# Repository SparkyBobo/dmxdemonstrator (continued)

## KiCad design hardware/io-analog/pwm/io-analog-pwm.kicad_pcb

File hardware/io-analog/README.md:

# DMX Demonstrator Analog IO Modules (DMX-IO2, DMX-IO3, DMX-IO4, DMX-IO5)

## Overview

The Analog IO Modules are a family of modules which generate analog signals. These modules are for use with the Receiver IO Module (DMX-RX2) and other DMX Demonstrator components. The Core module (DMX-IO2) convert the DMX signal into a 0 to +2.5V signal which the other modules then use to generate (more) useful signals. The other modules stack on top of the Core module and are designed to by used at the same time, so you can create a stack of any number of modules with DMX-IO2 on the bottom to generate a variety of signals. Each module will produce its signal in response to channels 1-4 and you can any of the signals, just pick off the signal you want from the appropriate module to control a device. You might use a stack of multiple modules if you wanted to coordinate channels 1-4 to control a variety of devices working in unison, such as a DIY moving head fixture.

## Signal options

### Core Module (DMX-IO2)

The Core module (DMX-IO2) convert the DMX signal into a 0 to +2.5V signal which the other modules then use to generate (more) useful signals. You can use the signal directly via the IO extension header.

### Voltage Module (DMX-IO3)

The Voltage IO module can generate a 0 to adjustable positive voltage which tracks the level of a channel. It is configurable to generate multiple output voltages to adapt it to any voltage range required. The default values
listed in the schematic generate 0 to +10V since this is a common lighting control signal.

### PWM Module (DMX-IO4)

The PWM IO module can generate a 0 to adjustable positive voltage PWM signal where the duty cycle tracks the level of a channel. It is configurable to generate multiple output voltages to adapt it to any voltage range required. The default values
listed in the schematic generate 0 to +10V since this is a common lighting control signal. The PWM IO module can also generate a 0 to +5V PWM signal where the duty cycle tracks the level of a channel. Both outputs can be used at the same time.

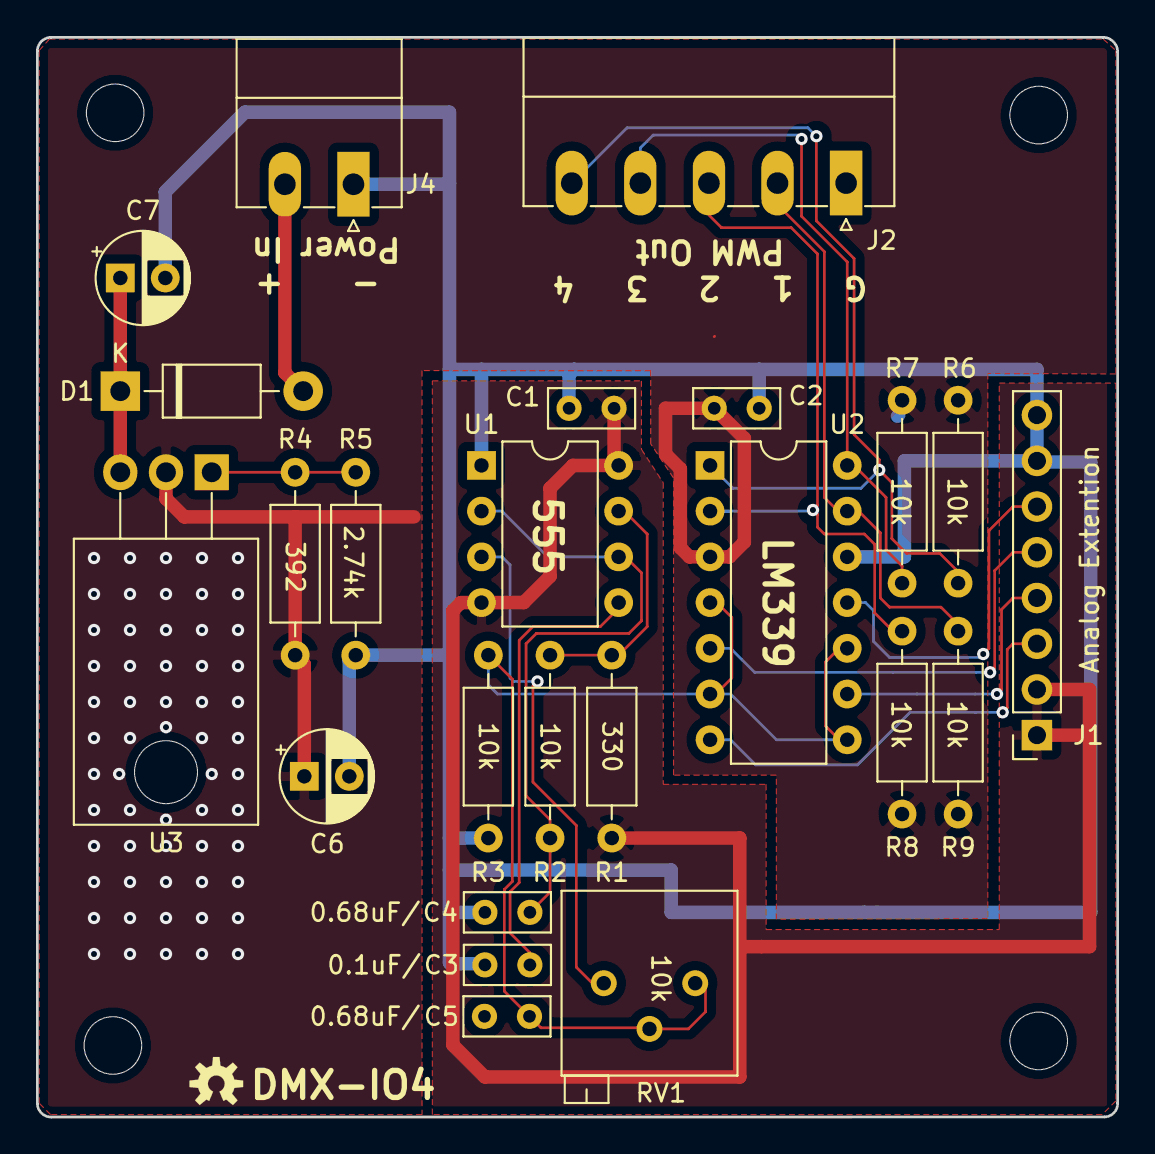
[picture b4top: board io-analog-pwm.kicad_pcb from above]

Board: 2 copper layers, 60.0 x 60.0 mm, 28 parts (0 on the bottom side), 19 nets.

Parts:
C1, C2, C3: 0.1uF; C_Rect_L4.6mm_W2.0mm_P2.50mm_MKS02_FKP02
C4, C5: 0.68uF; C_Rect_L4.6mm_W2.0mm_P2.50mm_MKS02_FKP02
C6, C7: 10uF; CP_Radial_D5.0mm_P2.50mm
D1: 1N5819; D_DO-41_SOD81_P10.16mm_Horizontal
J1: Analog Extension; PinSocket_1x08_P2.54mm_Vertical
J2: Output; PhoenixContact_MC_1,5_5-G-3.81_1x05_P3.81mm_Horizontal
J4: Power; PhoenixContact_MC_1,5_2-G-3.81_1x02_P3.81mm_Horizontal
MH1, MH2, MH3, MH4: MountingHole; MountingHole_3.2mm_M3
R1: 330; R_Axial_DIN0207_L6.3mm_D2.5mm_P10.16mm_Horizontal
R2, R3, R6, R7, R8, R9: 10k; R_Axial_DIN0207_L6.3mm_D2.5mm_P10.16mm_Horizontal
R4: 392 1%; R_Axial_DIN0207_L6.3mm_D2.5mm_P10.16mm_Horizontal
R5: 2.74k 1%; R_Axial_DIN0207_L6.3mm_D2.5mm_P10.16mm_Horizontal
RV1: 10k; Potentiometer_Bourns_3299P_Horizontal
U1: NE555; DIP-8_W7.62mm
U2: LM339; DIP-14_W7.62mm
U3: LM317T; TO-220-3_Horizontal_TabDown

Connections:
+5V: C1.1, J1.1, J1.2, R1.1, U1.4, U1.8
/AO0: J1.6, U2.11
/AO1: J1.5, U2.5
/AO2: J1.4, U2.9
/AO3: J1.3, U2.7
GND: C1.2, C2.2, C3.1, C4.1, C5.2, C6.2, C7.2, J1.7, J1.8, J2.1, J4.1, R3.1, R5.1, U1.1, U2.12
unnamed: C3.2, U1.5
unnamed: C4.2, R2.2, U1.2, U1.6
unnamed: C5.1, R3.2, RV1.2, RV1.3, U2.4, U2.6, U2.8, U2.10
unnamed: C7.1, D1.1, U3.3
unnamed: D1.2, J4.2
unnamed: J2.2, R9.2, U2.13
unnamed: J2.3, R8.2, U2.2
unnamed: J2.4, R7.2, U2.14
unnamed: J2.5, R6.2, U2.1
unnamed: R1.2, R2.1, U1.7
unnamed: R4.1, R5.2, U3.1
unnamed: RV1.1, U1.3
VDC: C2.1, C6.1, R4.2, R6.1, R7.1, R8.1, R9.1, U2.3, U3.2

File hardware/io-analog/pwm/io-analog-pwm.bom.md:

# Bill Of Materials (BOM)

## Schematic

**Filename:** E:\OpenSource\dmxdemonstrator\hardware\io-analog\pwm\io-analog-pwm.sch

**Date Modified:** 4/11/2024 8:56:17 PM

**Kicad Version:** Eeschema (5.1.12)-1

**Component Count:** 25

## Components

Item#|Quantity|Reference|Description|Manufacturer|Part Number|Datasheet|Notes
-----|--------|---------|-----------|------------|-----------|---------|-----
1|1|PCB|Analog IO PWM PCB|OHSPark|DMX-IO4, Rev 1.4||[Order](https://oshpark.com/shared_projects/xqcuVAnE)|
2|3|C1, C2, C3|0.1uF||||
3|2|C4, C5|0.68uF||||
4|2|C6, C7|10uF||||
5|1|D1|Schottky Diode, 40V 1A|Vishay General Semiconductor|1N5819|[Data Sheet](http://www.vishay.com/docs/88525/1n5817.pdf)|
6|1|J1|0.1 Female header, stacking||||
7|1|J2|Screw Terminal, 5 pin, 3.81 pitch|Phoenix Contact|1803303||
8|1|J2|Screw Terminal Plug, 5 pin, 3.81 pitch|Phoenix Contact|1840395||
9|1|J4|Screw Terminal, 2 pin, 3.81 pitch|Phoenix Contact|1803277||
10|1|J4|Screw Terminal Plug, 2 pin, 3.81 pitch|Phoenix Contact|1803578||
11|1|R1|330 ohm||||
12|2|R2, R3|10k ohm||||
13|1|R4|392 ohm 1% resistor||||
14|1|R5|2.74k 1% resistor||||
15|1|RV1|10k trimmer pot|Bourns|3299P-1-103LF|[Data Sheet](https://www.bourns.com/docs/Product-Datasheets/3299.pdf)|
16|1|U1|555 Precision Timer|Texas Instruments|NE555|[Data Sheet](https://www.ti.com/lit/ds/symlink/ne555.pdf)|
17|1|U2|Quad Differential Comparator|Texas Instruments|LM339|[Data Sheet](http://www.ti.com/lit/ds/symlink/lm339.pdf)|
18|1|U3|Linear Regulator, Adjustable, 1.5A TO220AB|STMicroelectronics|LM317T|[Data Sheet](http://www.st.com/content/ccc/resource/technical/document/da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|
<!--BOMROW-->

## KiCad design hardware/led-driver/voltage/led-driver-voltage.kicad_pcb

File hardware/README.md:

# DMX Demonstrator Hardware

## Overview

The DMX Demonstrator hardware folder contains various transmitters, receivers, and modules which all for the control of brightness of 4 channels of dimming.

## Status

Each hardware folder will contain a readme explaining the details of the component and it's status. The following is a definition of some common status:

- 

The _verified_ badge indicates that the component has been built and tested for use with the DMX Demonstrator family and is safe to build.

- 

The _testing_ badge indicates that the component has completed the design and prototype phase and being verified for use with the DMX Demonstrator family. It usually is assigned to a component revision for which the previous version is _verified_.

- 

The _prototype_ badge indicates that the component has completed the design phase and is being built and tested for use with the DMX Demonstrator family.

- 

The _design_ badge indicates that the component is still being design. has completed the design phase.

## Compatibility

For the components which connect to an Arduino, the readme provides a list of known compatible Arduino platforms. The DMX Demonstrator family will likely work with most Arduino boards, real or clones, but if you are having an
[issue](https://github.com/SparkyBobo/dmxdemonstrator/issues) with a particular board, open an issue to ask for verification. Please provide as much detail on the board and where is was obtained as possible.
Most compatibility issues are resolved by updating the software and do not require hardware revisions.

The following is a definition of some compatibilities:

- 

The _verified_ badge indicates that the component has been built and tested for the specific Arduino board.

- 

The _testing_ badge indicates that the component is being tested to determine if it is compatible with the specific Arduino board.

- 

The _research_ badge indicates that the component is being researched to determine if it is compatible with the specific Arduino board.

- 

The _incompatible_ badge indicates that the component is not compatible for the specific Arduino board.

## PCBs and Parts

I specify specific parts and pcbs in many places where other options will work just fine. You can find some notes as to why in [pcb.md](pcb.md) and [parts.md](parts.md).

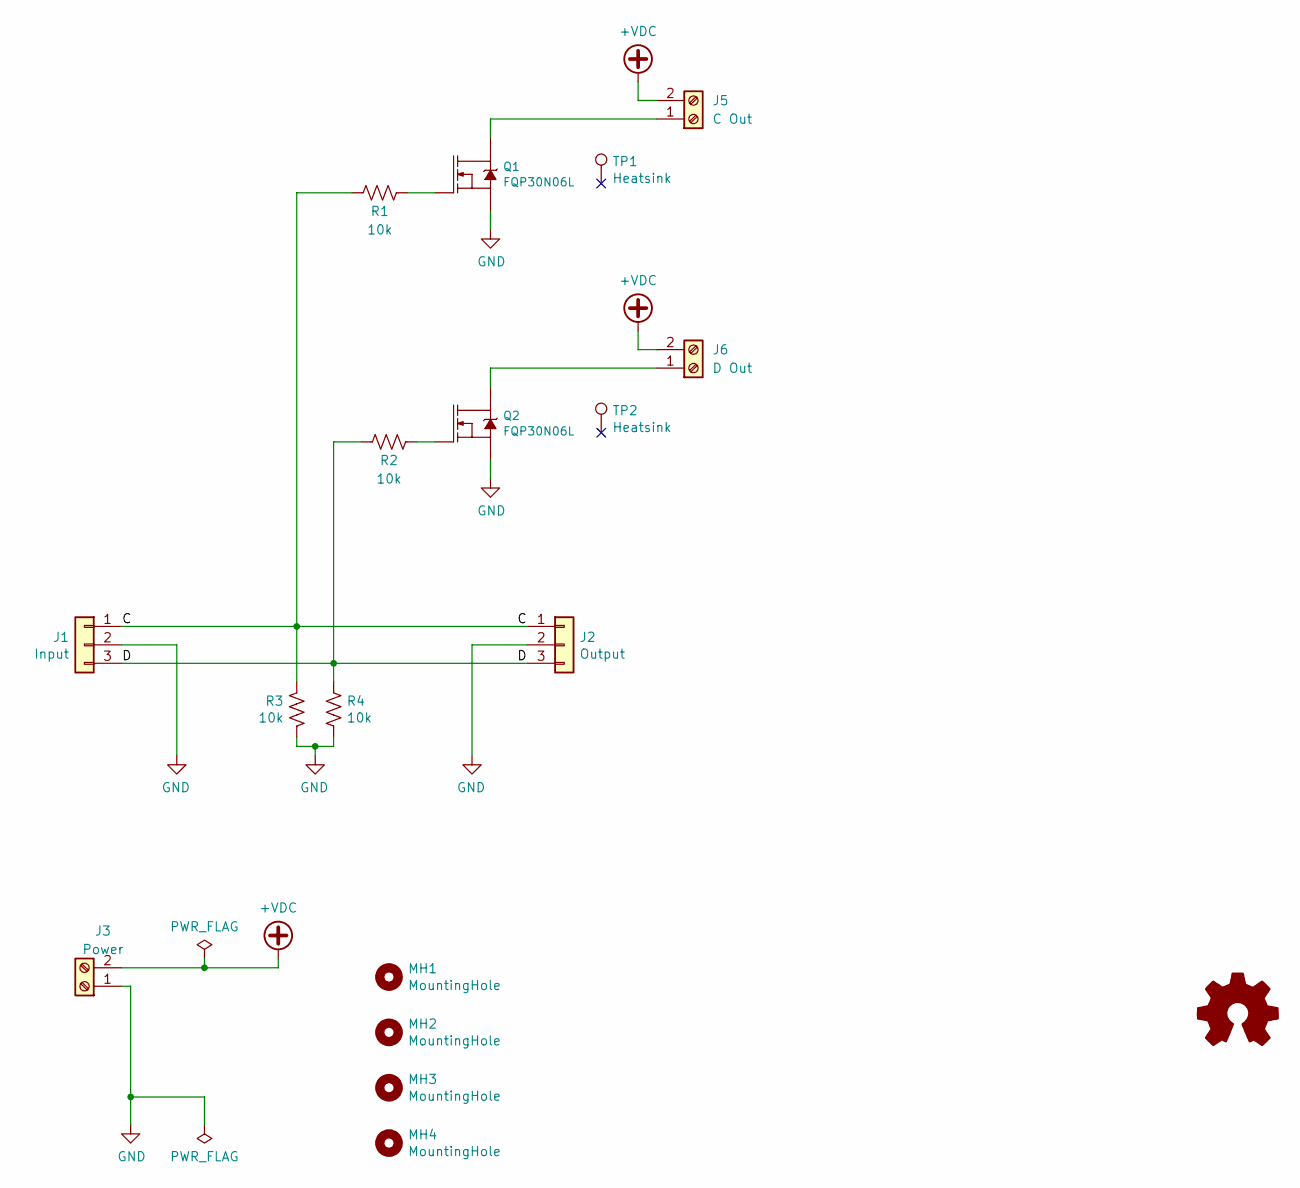
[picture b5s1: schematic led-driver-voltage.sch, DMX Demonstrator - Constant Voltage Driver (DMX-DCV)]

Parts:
J1: Input; PinHeader_1x03_P2.54mm_Horizontal
J2: Output; PinHeader_1x03_P2.54mm_Horizontal
J3: Power; PhoenixContact_MC_1,5_2-G-3.81_1x02_P3.81mm_Horizontal
J5: C Out; PhoenixContact_MC_1,5_2-G-3.81_1x02_P3.81mm_Horizontal
J6: D Out; PhoenixContact_MC_1,5_2-G-3.81_1x02_P3.81mm_Horizontal
MH1, MH2, MH3, MH4: MountingHole; MountingHole_3.2mm_M3
Q1, Q2: FQP30N06L; TO-220-3_Horizontal_TabDown
R1, R2, R3, R4: 10k; R_Axial_DIN0207_L6.3mm_D2.5mm_P10.16mm_Horizontal
TP1, TP2: Heatsink; TestPoint_Pad_D1.0mm

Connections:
+VDC: J3.2, J5.2, J6.2
/C: J1.1, J2.1, R1.2, R3.2
/D: J1.3, J2.3, R2.2, R4.1
GND: J1.2, J2.2, J3.1, Q1.3 (S), Q2.3 (S), R3.1, R4.2
unnamed: J5.1, Q1.2 (D)
unnamed: J6.1, Q2.2 (D)
unnamed: Q1.1 (G), R1.1
unnamed: Q2.1 (G), R2.1

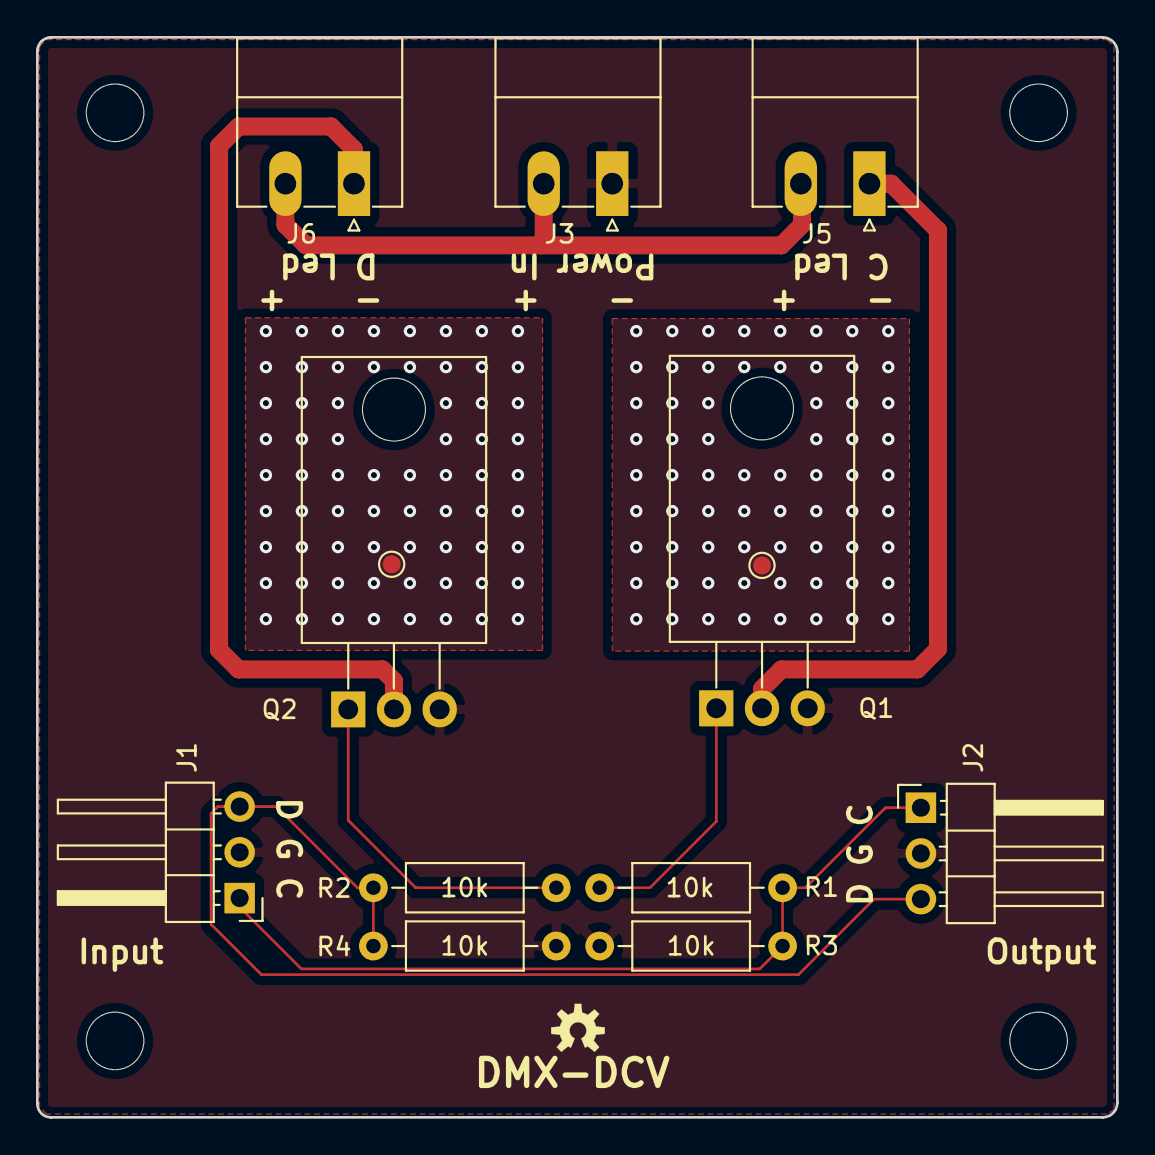
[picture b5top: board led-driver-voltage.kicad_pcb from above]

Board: 2 copper layers, 60.0 x 60.0 mm, 17 parts (0 on the bottom side), 8 nets.

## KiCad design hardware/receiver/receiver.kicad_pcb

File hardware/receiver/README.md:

# DMX Demonstrator Receiver (DMX-RX1)

## Status : Testing

## Overview

The Receiver is an [Arduino](https://www.arduino.cc/) Shield which accepts the 3-wire data/clock signal from the Transmitter (DMX-TX1) and decodes the data stream to control the brightness of 4 LEDs.

## Online parts list

For a complete list of parts, see:

- [Bill of materials](receiver.bom.md)
- [Part lists](receiver.parts.md)

You can also buy the parts for the Receiver online from a Wishlist:

- Sparkfun: [Common](https://www.sparkfun.com/wish_lists/160406), [DMX-RX1](https://www.sparkfun.com/wish_lists/160542)
- Adafruit: [Common](http://www.adafruit.com/wishlists/589832), [DMX-RX1](https://www.adafruit.com/wishlists/589834)

The Receiver needs parts from the common parts list but there are enough parts left over to build a Transmitter (DMX-TX1), Transmitter IO (DMX-TX2), and Frame Scrambler (DMX-FS1).

## PCB

You can order the PCB from [OHS Park](https://oshpark.com/):

- [DMX-RX1, Rev 1.4](https://oshpark.com/shared_projects/KHwUs20e).

You can read more about ordering pcbs [here](../pcb.md).

- ## Compatibility

 The DMX-RX1 is compatible with the following Arduino platforms:

- Arduino Uno R3: Hardware Revision 1.1+, Software Version 1.1+
- Arduino Leonardo: Hardware Revision 1.1+, Software Version  1.1+
- Arduino Mega or Mega 2560: Hardware Revision 1.1+, Software Version 1.2+

## Version History

### Rev 1.4

- Add PWM headers for use with led drivers

### Rev 1.3

- Remove PWM connector

### Rev 1.2

- Moved clock LED to avoid Arduino ICSP connector.
- Add RXCLK to D9 connection for Leonardo PCINT5.

### Rev 1.1

- Fixed shield footprint
- Added error and start code LEDs.
- Added Fcu power plane
- Redid Fcu layout
- Added rounded corners

### Rev 1.0

- Initial draft

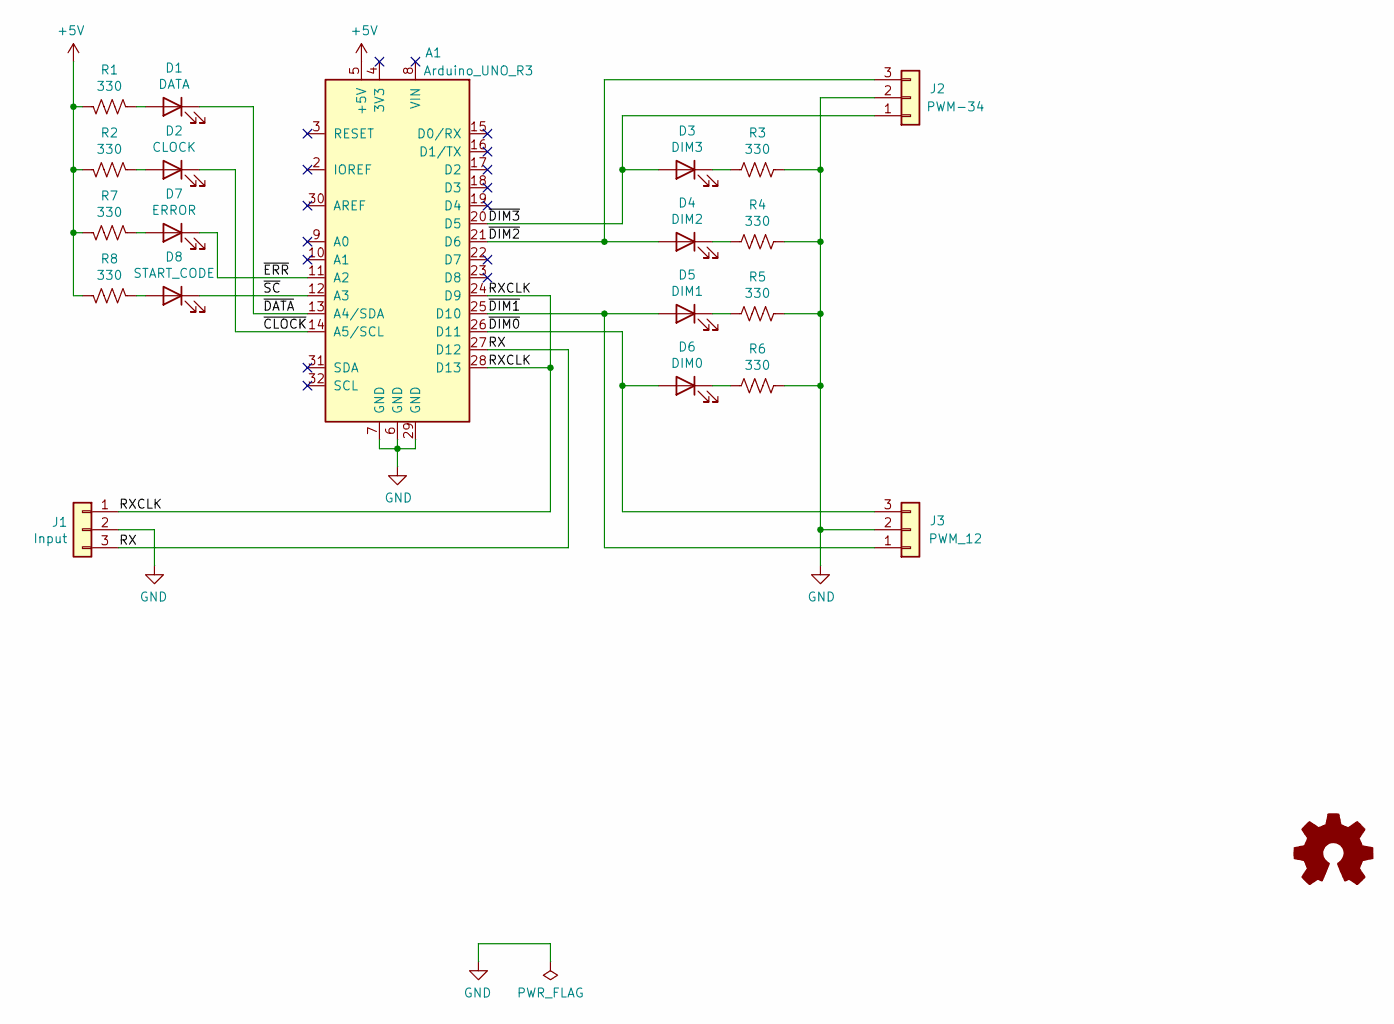
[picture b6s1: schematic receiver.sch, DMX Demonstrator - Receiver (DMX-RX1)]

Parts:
A1: Arduino_UNO_R3; ARDUINO_R3_NO_HOLES
D1: DATA; LED_D5.0mm
D2: CLOCK; LED_D5.0mm
D3: DIM3; LED_D5.0mm
D4: DIM2; LED_D5.0mm
D5: DIM1; LED_D5.0mm
D6: DIM0; LED_D5.0mm
D7: ERROR; LED_D5.0mm
D8: START_CODE; LED_D5.0mm
J1: Input; PinHeader_1x03_P2.54mm_Horizontal
J2: PWM-34; PinHeader_1x03_P2.54mm_Horizontal
J3: PWM_12; PinHeader_1x03_P2.54mm_Horizontal
R1, R2, R3, R4, R5, R6, R7, R8: 330; R_Axial_DIN0207_L6.3mm_D2.5mm_P10.16mm_Horizontal

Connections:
+5V: A1.5 (+5V), R1.1, R2.1, R7.1, R8.1
/RX: A1.27 (D12), J1.3
/RXCLK: A1.24 (D9), A1.28 (D13), J1.1
/~CLOCK: A1.14 (A5/SCL), D2.1 (K)
/~DATA: A1.13 (A4/SDA), D1.1 (K)
/~DIM0: A1.26 (D11), D6.2 (A), J3.3
/~DIM1: A1.25 (D10), D5.2 (A), J3.1
/~DIM2: A1.21 (D6), D4.2 (A), J2.3
/~DIM3: A1.20 (D5), D3.2 (A), J2.1
/~ERR: A1.11 (A2), D7.1 (K)
/~SC: A1.12 (A3), D8.1 (K)
GND: A1.6 (GND), A1.7 (GND), A1.29 (GND), J1.2, J2.2, J3.2, R3.1, R4.1, R5.1, R6.1
unnamed: D1.2 (A), R1.2
unnamed: D2.2 (A), R2.2
unnamed: D3.1 (K), R3.2
unnamed: D4.1 (K), R4.2
unnamed: D5.1 (K), R5.2
unnamed: D6.1 (K), R6.2
unnamed: D7.2 (A), R7.2
unnamed: D8.2 (A), R8.2

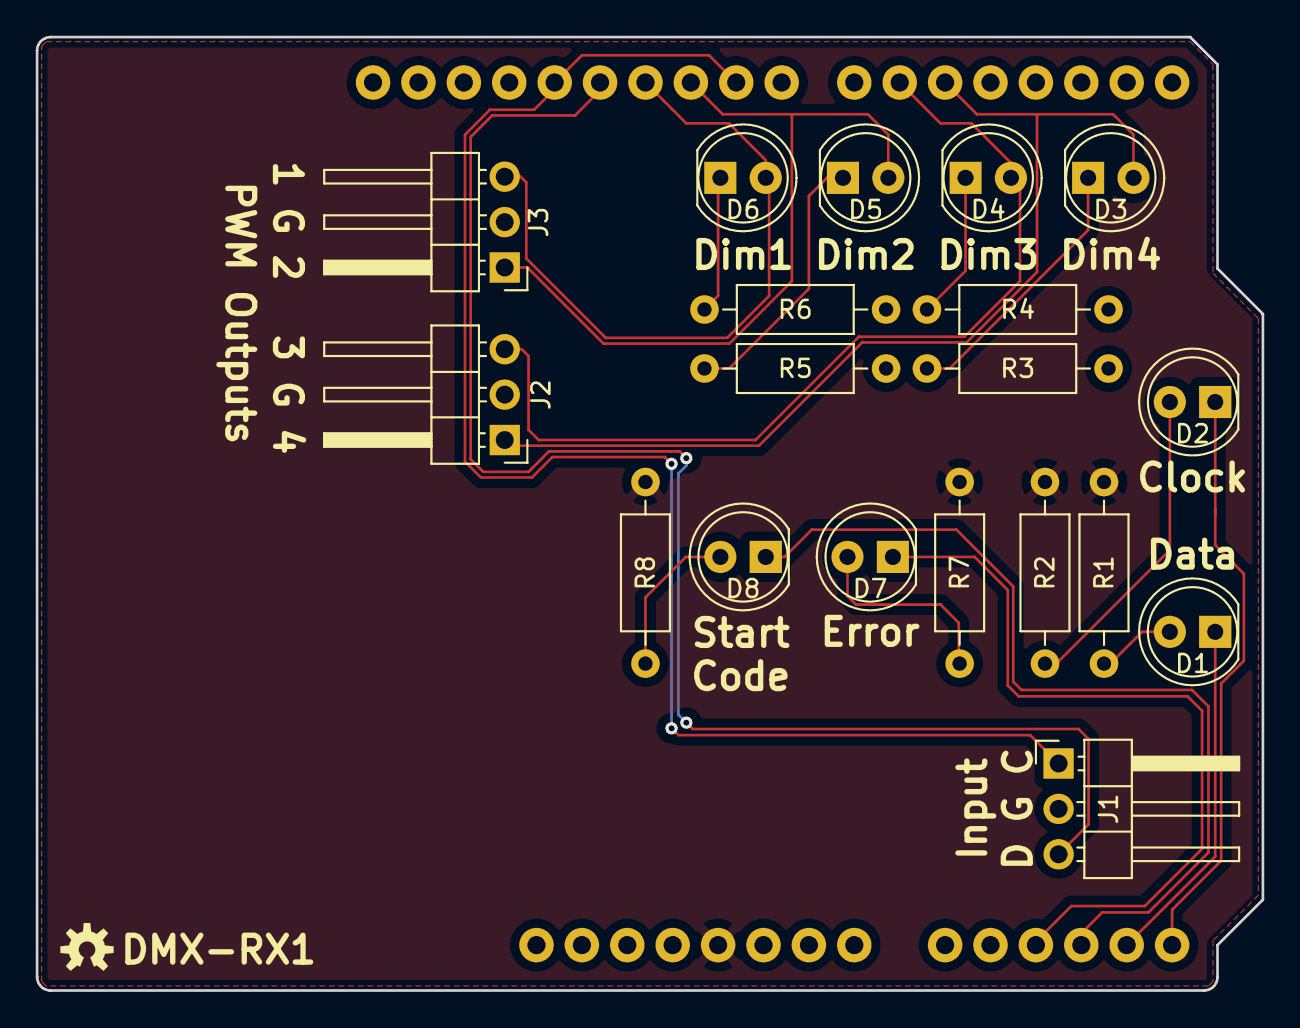
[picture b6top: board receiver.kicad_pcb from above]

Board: 2 copper layers, 68.6 x 53.3 mm, 20 parts (0 on the bottom side), 20 nets.

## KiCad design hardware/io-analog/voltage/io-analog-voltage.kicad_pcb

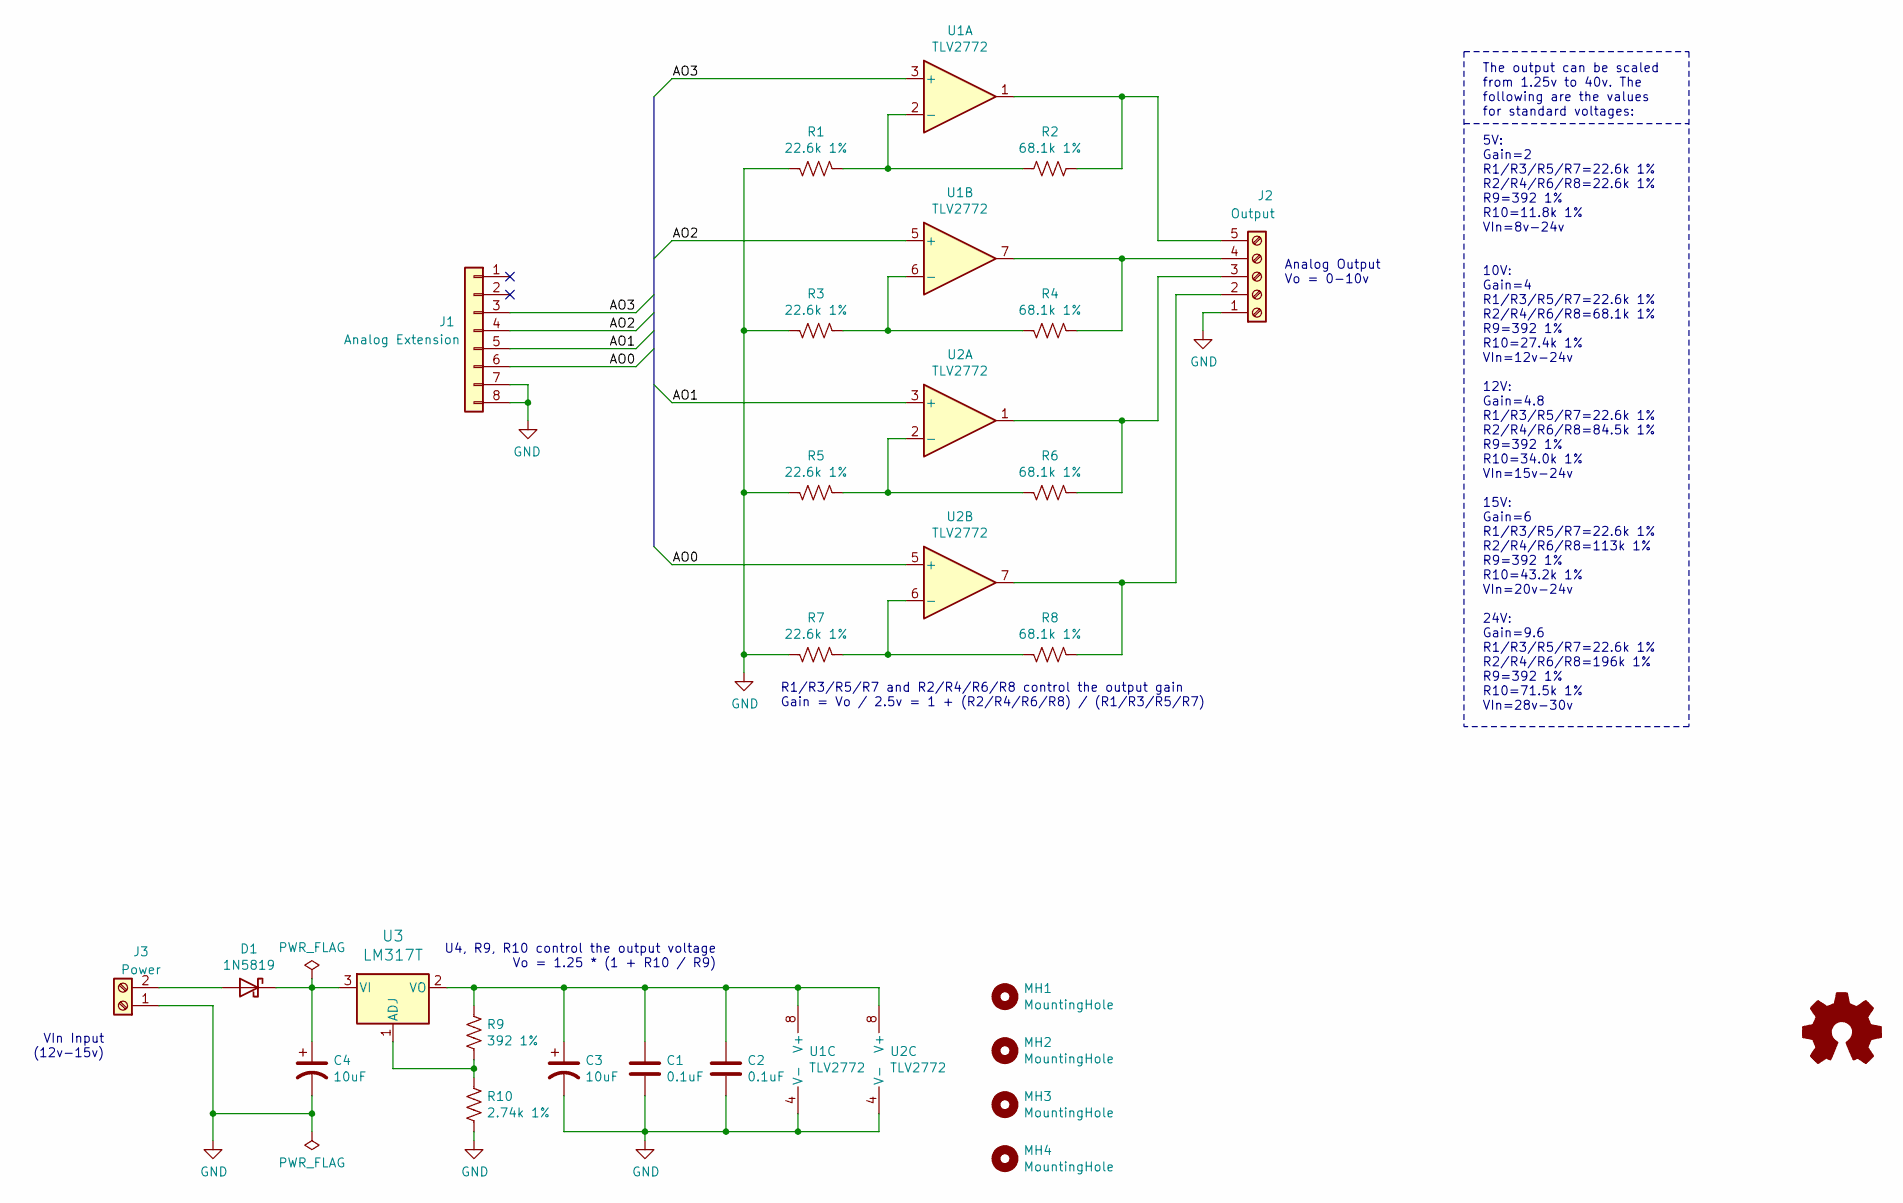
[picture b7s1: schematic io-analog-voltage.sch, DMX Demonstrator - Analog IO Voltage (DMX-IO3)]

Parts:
C1, C2: 0.1uF; C_Rect_L4.6mm_W2.0mm_P2.50mm_MKS02_FKP02
C3, C4: 10uF; CP_Radial_D5.0mm_P2.50mm; Digi-Key_PN P10425CT-ND
D1: 1N5819; D_DO-41_SOD81_P10.16mm_Horizontal; Digi-Key_PN 1N5819-E3/54GITR-ND
J1: Analog Extension; PinSocket_1x08_P2.54mm_Vertical
J2: Output; PhoenixContact_MC_1,5_5-G-3.81_1x05_P3.81mm_Horizontal; Digi-Key_PN 277-1109-ND
J3: Power; PhoenixContact_MC_1,5_2-G-3.81_1x02_P3.81mm_Horizontal; Digi-Key_PN 277-1106-ND
MH1, MH2, MH3, MH4: MountingHole; MountingHole_3.2mm_M3
R1, R3, R5, R7: 22.6k 1%; R_Axial_DIN0207_L6.3mm_D2.5mm_P10.16mm_Horizontal; Digi-Key_PN 22.6KXBK-ND
R2, R4, R6, R8: 68.1k 1%; R_Axial_DIN0207_L6.3mm_D2.5mm_P10.16mm_Horizontal; Digi-Key_PN 68.1KXBK-ND
R9: 392 1%; R_Axial_DIN0207_L6.3mm_D2.5mm_P10.16mm_Horizontal; Digi-Key_PN 392XBK-ND
R10: 2.74k 1%; R_Axial_DIN0207_L6.3mm_D2.5mm_P10.16mm_Horizontal; Digi-Key_PN 13-MFR-25FRF52-2K74TR-ND
U1, U2: TLV2772; DIP-8_W7.62mm; Digi-Key_PN 296-7592-5-ND
U3: LM317T; TO-220-3_Horizontal_TabDown; MPN LM317T; Digi-Key_PN 497-1575-5-ND

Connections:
/AO0: J1.6, U2.5 (+)
/AO1: J1.5, U2.3 (+)
/AO2: J1.4, U1.5 (+)
/AO3: J1.3, U1.3 (+)
GND: C1.2, C2.2, C3.2, C4.2, J1.7, J1.8, J2.1, J3.1, R1.1, R3.1, R5.1, R7.1, R10.1, U1.4 (V-), U2.4 (V-)
unnamed: C1.1, C2.1, C3.1, R9.2, U1.8 (V+), U2.8 (V+), U3.2 (VO)
unnamed: C4.1, D1.1 (K), U3.3 (VI)
unnamed: D1.2 (A), J3.2
unnamed: J2.2, R8.2, U2.7
unnamed: J2.3, R6.2, U2.1
unnamed: J2.4, R4.2, U1.7
unnamed: J2.5, R2.1, U1.1
unnamed: R1.2, R2.2, U1.2 (-)
unnamed: R3.2, R4.1, U1.6 (-)
unnamed: R5.2, R6.1, U2.2 (-)
unnamed: R7.2, R8.1, U2.6 (-)
unnamed: R9.1, R10.2, U3.1 (ADJ)

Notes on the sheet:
R1/R3/R5/R7 and R2/R4/R6/R8 control the output gain Gain = Vo / 2.5v = 1 + (R2/R4/R6/R8) / (R1/R3/R5/R7)
VIn Input (12v-15v)
The output can be scaled from 1.25v to 40v. The following are the values for standard voltages: 5V: Gain=2 R1/R3/R5/R7=22.6k 1% R2/R4/R6/R8=22.6k 1% R9=392 1% R10=11.8k 1% VIn=8v-24v 10V: Gain=4 R1/R3/R5/R7=22.6k 1% R2/R4/R6/R8=68.1k 1% R9=392 1% R10=27.4k 1% VIn=12v-24v 12V: Gain=4.8 R1/R3/R5/R7=2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
Analog Output Vo = 0-10v
U4, R9, R10 control the output voltage Vo = 1.25 * (1 + R10 / R9)

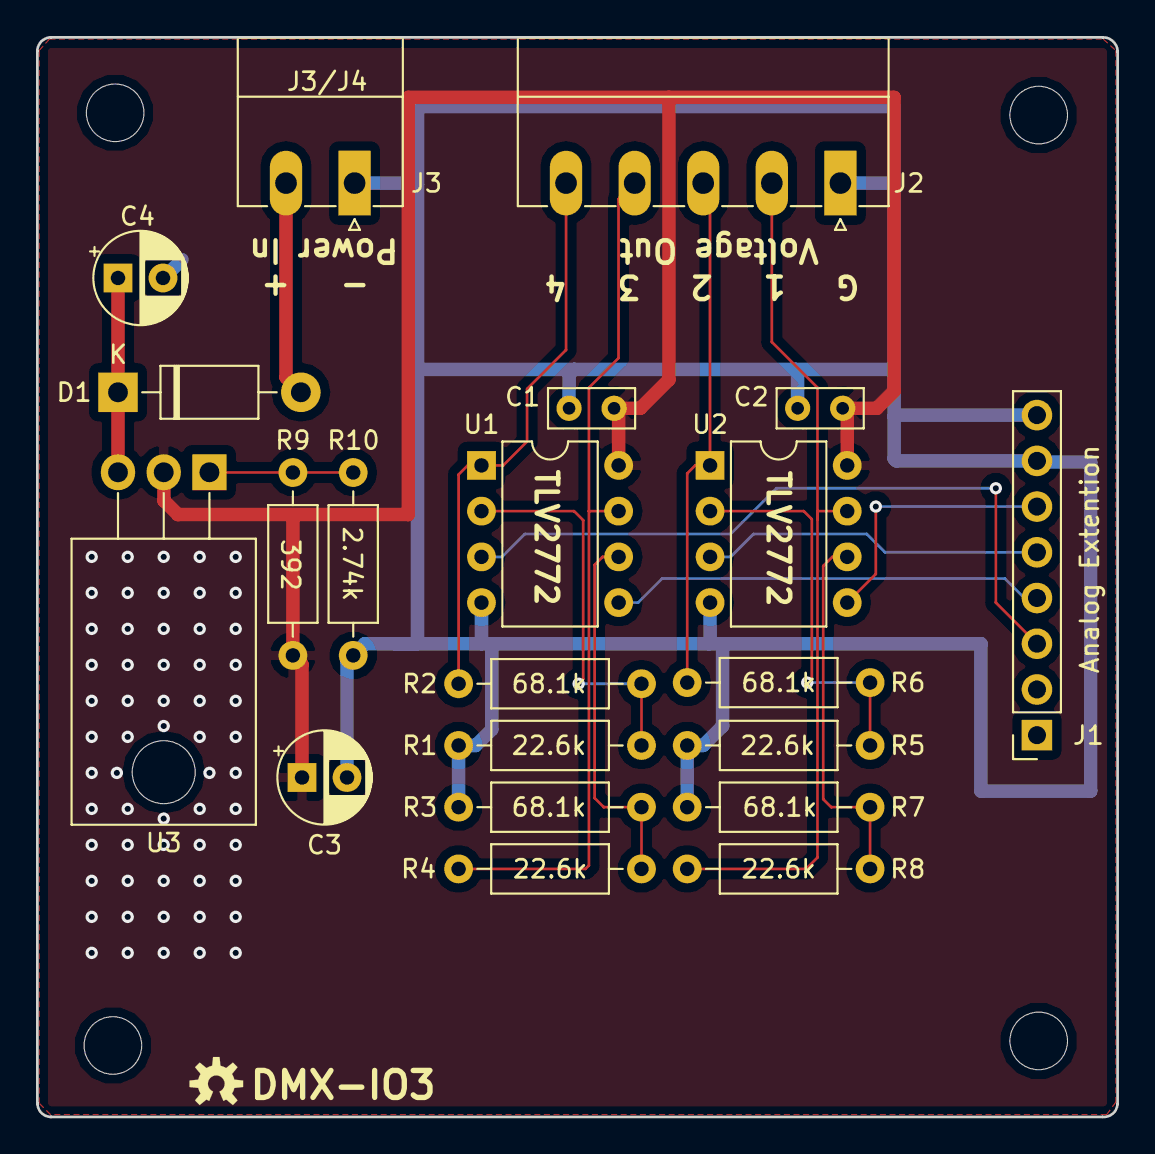
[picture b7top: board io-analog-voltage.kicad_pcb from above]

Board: 2 copper layers, 60.0 x 60.0 mm, 25 parts (0 on the bottom side), 17 nets.

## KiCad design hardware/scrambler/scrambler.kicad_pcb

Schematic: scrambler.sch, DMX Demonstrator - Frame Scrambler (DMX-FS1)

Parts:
A1: Arduino_UNO_R3; ARDUINO_R3_NO_HOLES
D1: DATA_OUT; LED_D5.0mm
D2: CLOCK_OUT; LED_D5.0mm
D3: DATA_IN; LED_D5.0mm
D4: CLOCK_IN; LED_D5.0mm
D5, D6: DIM1; LED_D5.0mm
J1: Input; PinHeader_1x03_P2.54mm_Horizontal
J2: Output; PinHeader_1x03_P2.54mm_Horizontal
J3: Display; PinHeader_1x03_P2.54mm_Horizontal
JP1: EN/RX; SolderJumper-3_P1.3mm_Bridged12_RoundedPad1.0x1.5mm_NumberL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
R1, R2, R3, R4, R5, R6, R7: 330; R_Axial_DIN0207_L6.3mm_D2.5mm_P10.16mm_Horizontal
S1: CLEAR; TACTILE_SWITCH_PTH_12MM
S2: SCRAMBLE; TACTILE_SWITCH_PTH_12MM
S3: ENABLE; TACTILE_SWITCH_PTH_12MM

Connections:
+5V: A1.5, R1.1, R2.1, R3.1, R4.1, R5.1, R6.1
/A1: A1.10, S1.3
/A2: A1.11, S2.3
/A3: A1.12, JP1.1 (A)
/A4: A1.13, J3.1
/A5: A1.14, S3.3
/EN: J3.3, JP1.2 (C)
/RX: A1.27, J2.3, JP1.3 (B)
/RXCLK: A1.28, J2.1
/TX: A1.23, J1.1
/TXCLK: A1.24, J1.3
/~CLK_RX: A1.18, D2.1 (K)
/~CLK_TX: A1.20, D4.1 (K)
/~DATA_RX: A1.17, D1.1 (K)
/~DATA_TX: A1.19, D3.1 (K)
/~EN: A1.22, D6.1 (K)
/~SCRAM: A1.21, D5.1 (K)
GND: A1.6, A1.7, A1.29, J1.2, J2.2, J3.2, R7.2, S1.1, S2.1, S3.1
unnamed: A1.25, A1.26, R7.1
unnamed: D1.2 (A), R1.2
unnamed: D2.2 (A), R2.2
unnamed: D3.2 (A), R3.2
unnamed: D4.2 (A), R4.2
unnamed: D5.2 (A), R5.2
unnamed: D6.2 (A), R6.2

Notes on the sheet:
Clear All
Scramble
Data In
Enable
Clock Out
Data Out
Clock In
Scrambled
Enabled

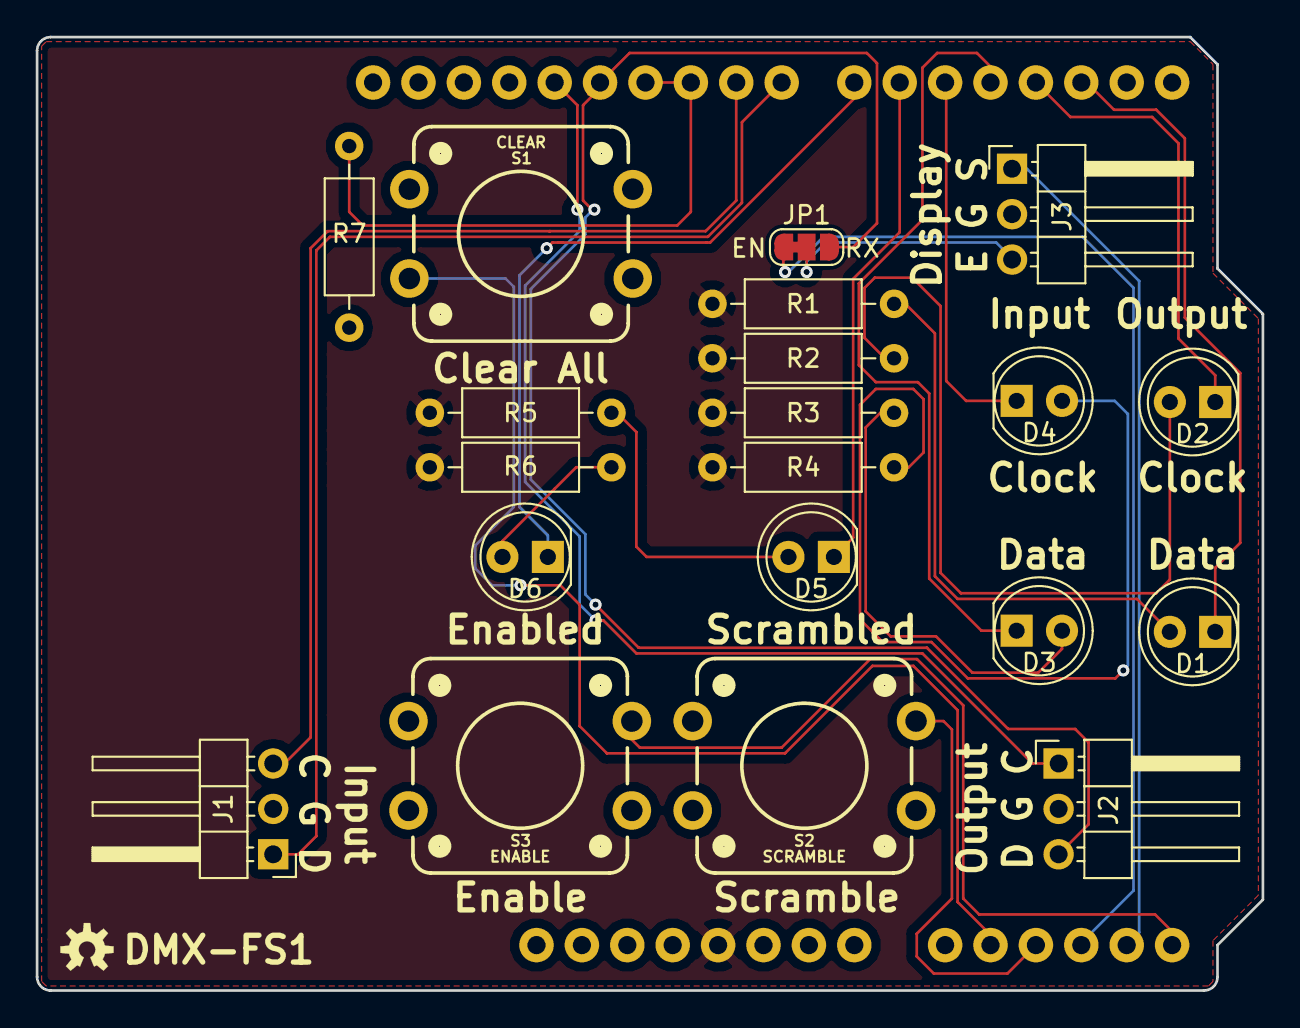
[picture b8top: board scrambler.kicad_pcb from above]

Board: 2 copper layers, 68.6 x 53.3 mm, 21 parts (0 on the bottom side), 25 nets.

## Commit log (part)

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2020-09-26 Update README.md
    Add readme
2020-09-26 Initial 1.0 version of transmitter.
2020-09-26 Initial 1.0 version of receiver.
2020-09-26 Initial 1.0 version of display-pro.
2020-09-26 Initial 1.0 version of control-pro.
2020-09-26 Initial 1.0 version of transmitter and receiver software.
2020-09-26 Add the original artifacts.
2020-09-26 Initial draft of transmitter-pro schematic.
2020-09-26 Initial draft of receiver-pro schematic.
2020-09-27 Add parts lists. Add PCB links. Fix silkscreen of connector J2 on DMX-TX2.
2020-09-27 Update README.md
    Update transmitter rotary pot part number.
2020-09-27 Enlarged 3rd slider slot width to remove copper from faceplate.
2020-09-27 Add revision number to all OHS Park links.
2020-09-29 Add rounded corners to control-pro.
2020-09-29 Initial version of analog dimmer.
2020-11-08 Rev 1.1: - Fixed arduino shield footprint (it was backwards) - Added Fcu power plane - New Fcu layouts - Added rounded corners
2020-11-09 Remove coax power jack from display-pro; the Sparkfun footprint does not nest inside the 2 pin connector so only providing that option.
2020-12-29 Add discovery sketch to determine attached board and test it.
2020-12-30 Refactor Transmitter, V1.1 * Move serial transmission out of the clock interrupt * Move timer code to libraries * Include JC_Button as a local library to make the code self-contained * Implement asyn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
2020-12-30 Refactor Receiver, V1.1 * Move serial transmission out of the clock interrupt * Move pin change code to libraries * Add verbose and compact status modes * Make variable naming consistent * Make comme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
2020-12-30 Add verbose and compact status modes
2020-12-30 Standardize on "step".
2021-01-22 v0.1 initial checkin.
2021-03-02 v0.2:
    Implemented navigation, configure, and demo UI in UIKit.
    Cleaned up navigation.
    Implemented board discovery (partial).
    Added new images.
2021-10-05 Add support for discovery of boards.
2022-09-06 Split RX-Pro into multi-sheet schematic.
2022-09-06 Add gitignore for desktop software.
2022-09-14 Users/sparky/txrx12 (#11)
    * TX1 1.2, RX1 1.2
    Move Clock LED to avoid ICSP connector.
    Align TX Fast/Slo clock LEDS and RX start code/error LEDs.
    * Add RXCLK to D9 connection for Leonardo PCINT5.
2022-09-14 Add part numbers.
2022-10-09 Split transmitter-pro into multiple projects/sheets.
2022-10-09 Add timing diagrams.
2023-02-08 Users/sparky/rx refactor (#12)
    * Refactor Receiver, V1.1
    * Move serial transmission out of the clock interrupt
    * Move pin change code to libraries
    * Add verbose and compact status modes
    * Make variable naming consistent
    * Make comment style consistent
2023-02-08 Users/sparky/tx refactor (#13)
    * Refactor Transmitter, V1.1
    * Move serial transmission out of the clock interrupt
    * Move timer code to libraries
    * Include JC_Button as a local library to make the code self-contained
    * Implement async analog capture
    * Make variable naming consistent
2023-02-08 Add discovery sketch to determine attached board and test it. (#14)
2023-02-08 Split receiver-pro into multiple projects/sheets.
2023-02-09 Fixes: (#15)
    - Slow down analog read clock
    - Fix bug on TX1 where dimmer value was written to all dimmers, not the selected dimmer
    - Fix bug where clock speed was using byte math instead of long math due to #define
    - Avoid going into error state when stream is in break at expected time
    - Disable verbose mode when the clock is too fast to keep up with writing the verbose output
2023-02-13 Add top level project Update part #s Update power sheets
2023-02-15 Update part numbers Swap out input connector footprint Placement tweaks
2023-02-15 Add rx-retro main project
2023-02-20 Add analog, pwm, dmx, and io boards. Still needs work.
2023-02-20 Move TX2 to tx-io
2023-03-03 Prototype version of DMX, Analog, and PWM IO Modules and both TX and RX IO interfaces.
2023-03-03 Fix badges Update display-pro readme
2023-03-03 Fix 2 more badges.
2023-03-05 Add Coax power back to display board. Save gerbers settings for rx1, tx1, tx2. Update dsp & rx1 schematic pdf.
2023-03-07 Ouptut local gerbers (ignored) Add detected LED to tx2
2023-06-01 Prototype and PCB layout for core Prototype and PCB layout for demo Prototype and PCB layout for control-eprom Move display design forward Refactor control-dmx to dmx Update expansion connector on al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
2023-06-01 Swap data order in analog Swap voltage refs in analog Add test suite
2023-07-09 Make io-analog a stackable family io-analog-core handles D to A io-analog-amplify handles voltage output io-analog-pwm handles pwm output for leds, drive display pro io-analog-led handles 5v pwm outp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
    Refactor display-pro to work with io-analog-pwm
    Add correct coax power connector
2023-07-09 Copies of temporary work.
2023-07-23 Finalize PWM and Voltage modules (1 each).
2023-07-23 Finalize io-analog boards.
2023-07-23 Finalize io-dmx board
2023-08-21 Added Bill Of Materials (BOM)
2023-09-17 Rev 1.1 - Value labels - 74LS06 led driver
2023-09-29 Use 74LS07 Led driver Add R5 for discovery.
2023-10-30 Display Pro: - Switch to smaller screw terminal connectors - Add pull-down resistors - Add silkscreen values - Remove COAX power connector...again - Add test software
    Core:
    - Fix issue with A03 and A02 being reversed at Analog Extensions
    - Fix issue with A1 and A0 at IO Extension header
    - Label D0..D7 correctly
    - Swap U4 and U5 in schematic to match board layout
    - Change TO-92 footprint
2023-12-06 Update silk screen.
2023-12-20 Tweaks boards based on construction notes
2023-12-23 Ignore gerber files.
2023-12-23 Removing test code for io-modules Will re-add with a better directory structure at a later time.
2023-12-24 Final tweaks to TX1 and RX1 based on construction. (#17)
    * Improve surface areea of power plane.
    * Add design badges
    Remove PWM connect from RX1
    Update TX1 board details
    commit 6da493b019dfdde530e2737d5f7a25deacfc908e
    Author: SparkyBobo <sparky@crazygiraffesoftware.com>
2023-12-24 Users/sparky/control pro v1.3 (#18)
    * DMX-TX2 V1.1:
    - Fixed shield footprint
    - Moved Clock LED to avoid Arduino ICSP connector.
    - Relabeled the clock fast and slow LED connections in the
    schematic to match the board layout.
    - Added Fcu power plane
2023-12-24 Initial draft of the FS-1 scrambler.
2024-01-08 Rev 1.1 of scrambler Software for scrambler
2024-02-03 Create constant voltage (formerly display-pro) led driver Create constant current led driver Add PWM outputs for led drivers to the receiver
2024-02-04 remove display-pro replaced by constant voltage led driver.
2024-02-04 Add PWM outs to the receiver.
2024-02-18 Rebranded.
2024-02-18 Add inductor footprint.
2024-02-18 Add mini mover files.
2024-02-18 Add modular mover files.
2024-02-18 Add to parts library .
2024-02-19 Rebrand to Sparky Bobo Designs
2024-02-19 FM's feedback.
2024-02-19 Remove branches.txt
2024-02-19 Remove non io-analog files. Rebrand.
2024-02-19 Update IO-analog readme.
2024-02-19 Revert schematics.
2024-02-19 Consolidate parts library. Rebrand.
2024-02-19 Remove non-dmx files. Rebrand.
2024-02-19 Remove more non-dmx files.
2024-02-20 Remove display-pro.
2024-02-20 Library fixup. Rebrand.
2024-02-20 Clean non-led files.
2024-02-20 Fixup libraries. Rebrand.
2024-03-09 Add dmx frame timing diagram
2024-03-09 Add break, start, and dimmer timings.
2024-03-17 Working version of demo software, MVP.
2024-03-17 Add receiver support for IO analog modules
2024-03-18 Get sketch working. Adding missing library.
2024-03-18 Rmove hard-coded start bit scramble
2024-03-18 Add software support for DMX options.
2024-03-18 Users/sparky/scrambler (#6)
    * Initial draft of the FS-1 scrambler.
    * Rev 1.1 of scrambler
    Software for scrambler
    * Fixup libraries.
    Rebrand.
    * Get sketch working.
2024-03-18 Working version of demo software, MVP. (#7)
2024-03-18 Add receiver software.
2024-03-18 Set pins to putput mode Cleanup
2024-03-18 Users/sparky/io analog (#3)
    * Make io-analog a stackable family
    io-analog-core handles D to A
    io-analog-amplify handles voltage output
    io-analog-pwm handles pwm output for leds, drive display pro
    io-analog-led handles 5v pwm output for iot, drive display pro
    Core:
2024-03-18 Fix issue where transmitter may not go to 0 when using TX2 Fixed discovery or TX1 and FS1 Fixed bug where FS1 didn't work on Uno Fixed bug where unplugged device has not handled well. Fix companion b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
2024-03-18 Fix issue where transmitter may not go to 0 when using TX2 (#8)
    Fixed discovery or TX1 and FS1
    Fixed bug where FS1 didn't work on Uno
    Fixed bug where unplugged device has not handled well.
    Fix companion bug where connection string did not clear old images
2024-03-20 Demo changes.
2024-03-25 Rename control-pro Update readmes Delete old pngs
2024-03-25 Add PWM headers on DMX-RX1.
2024-03-25 Hardware Cleanup (#20)
    * Rename control-pro
    Update readmes
    Delete old pngs
    * Add PWM headers on DMX-RX1.
2024-03-25 Demo changes. (#21)
2024-04-08 Add BOM generator Add BOM and parts .md's
2024-04-08 Users/sparky/hwcleanup (#22)
    * Rename control-pro
    Update readmes
    Delete old pngs
    * Add PWM headers on DMX-RX1.
    * Add BOM generator
    Add BOM and parts .md's
2024-04-14 Add parts and BOMs for rest of boards. Cleanup .md files.
2024-04-14 Cleanup PWM voltage options.
2024-04-14 Remove PWM's J3 in preperation for deleting it in Rev 1.5. It serves little purpose, no need to populate it in Rev 1.4.
2024-04-14 Revert .parts.md to Rev 1.4 version.
2024-04-14 - Added pullup resistors. - Removed J3.
2024-04-14 Set status to prototype.
2024-04-14 Update schematic pdf.
2024-04-21 Add parts and BOMs for rest of boards. (#24)
    * Add parts and BOMs for rest of boards.
    Cleanup .md files.
    * Cleanup PWM voltage options.
    * Remove PWM's J3 in preperation for deleting it in Rev 1.5.
    It serves little purpose, no need to populate it in Rev 1.4.
2024-04-22 - Added termination switch - Change to RFM-0505S - Change to MAX485E - Swap A and B on Max485 - Avoid split power planes under WH4 - Remove pads from XLR alignment pins - Update readme - Add IO1 part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
2024-04-22 Update PCB links in readme, bom, parts Update U1 part links in readme
2024-04-25 Create constant current led driver
2024-05-25 Breakup TX2 into 2 boards, allowing IO boards to be used with TX1.
2024-05-25 Add correct board to parts.json
2024-05-25 Verify Adafruit parts for DMX-TX1.
2024-05-25 Verify Adafruit parts for DMX-TX1. (#27)
2024-05-26 Remove extras silk screen test.
2024-06-12 Add DMX-IO1, DMX-512 support - Added termination switch - Change to RFM-0505S - Change to MAX485E - Swap A and B on Max485 - Avoid split power planes under WH4 - Remove pads from XLR alignment pins -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
2024-06-12 Add DMX-IO1, DMX-512 support - Added termination switch - Change to RFM-0505S - Change to MAX485E - Swap A and B on Max485 - Avoid split power planes under WH4 - Remove pads from XLR alignment pins -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
2024-06-22 Put text on Back Silk instead of Front Mask.
2024-06-25 Fix inductor part/quantity. Mark as verified. Delete old readme
2024-06-25 Mark as verified.
2024-06-25 DMX-IO4, Rev 1.5 (#25)
    * Add parts and BOMs for rest of boards.
    Cleanup .md files.
    * Cleanup PWM voltage options.
    * Remove PWM's J3 in preperation for deleting it in Rev 1.5.
    It serves little purpose, no need to populate it in Rev 1.4.
    * Revert .parts.md to Rev 1.4 version.
2024-06-25 Users/sparky/io analog led (#5)
    * Create constant current led driver
    * Add correct board to parts.json
    * Fix inductor part/quantity.
    Mark as verified.
    Delete old readme
2024-07-30 Update board link. Mark as verified.
2024-07-30 Add serial output for DMX mode.
2024-08-04 Remove #if for DMX-512 support. Mark verified.
2024-08-04 Users/sparky/dmxio1 rev1 7 (#28)
    * Add DMX-IO1, DMX-512 support
    - Added termination switch
    - Change to RFM-0505S
    - Change to MAX485E
    - Swap A and B on Max485
    - Avoid split power planes under WH4
2024-09-30 Release 1.0.0.
